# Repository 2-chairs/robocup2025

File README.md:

# robocup2025
# Team 2-Chairs - RoboCup Singapore Soccer Open Junior 

*Repository for the official electronic, mechanical, and software files of Team 2-Chairs.*

## About

This repository is for **Team 2-Chairs**, a Singapore RoboCup Open Soccer Junior team, and includes relevant design files and resources.

## Repository Structure

- **Electronics/** - PCB designs, schematics, and component footprints. (Note: regarding layer1 and layer3 pcb files, a critical mistake had been made where the Xiao Esp32c3 was powered through 3v3 pin with 3v3, when it should have been through 5v VIN pin with 5v; regarding layer3 the camera should be powered through 5v instead of 3v3 too)
- **Mechanical/** - 3D-printable files in **.3MF** and **.STL** formats; includes rendered images of the robot and its mirrored counterpart for reference. 
- **Code/** - Firmware and control software for the robot. (sub-par quality, some code untested)
- **Logo/** - Official team branding and design assets.

## Credits 
In the grand tapestry of our design endeavor, we owe a debt of profound gratitude to the esteemed teams of Sentinels Robotics, ducc. & Butter Chicken, whose brilliant schematics and designs (and potentially code) have guided our efforts.

## License & Copyright

© 2025 Team 2-Chairs. All rights reserved, except where otherwise stated. 

<p xmlns:cc="http://creativecommons.org/ns#" ><a rel="cc:attributionURL" href="https://github.com/2-chairs/robocup2025">This work</a> by <span property="cc:attributionName">Ng Chen-Xuan, Euston Tan, Chen YiKai</span> is licensed under <a href="https://creativecommons.org/licenses/by-nc-sa/4.0/?ref=chooser-v1" target="_blank" rel="license noopener noreferrer" style="display:inline-block;">Creative Commons Attribution-NonCommercial-ShareAlike 4.0 International</a></p>

---

**"Two chairs, twice the betterness"**

*Written by ChatGPT, Edited by human*

<p>Retired as of 6 April 2025</p>

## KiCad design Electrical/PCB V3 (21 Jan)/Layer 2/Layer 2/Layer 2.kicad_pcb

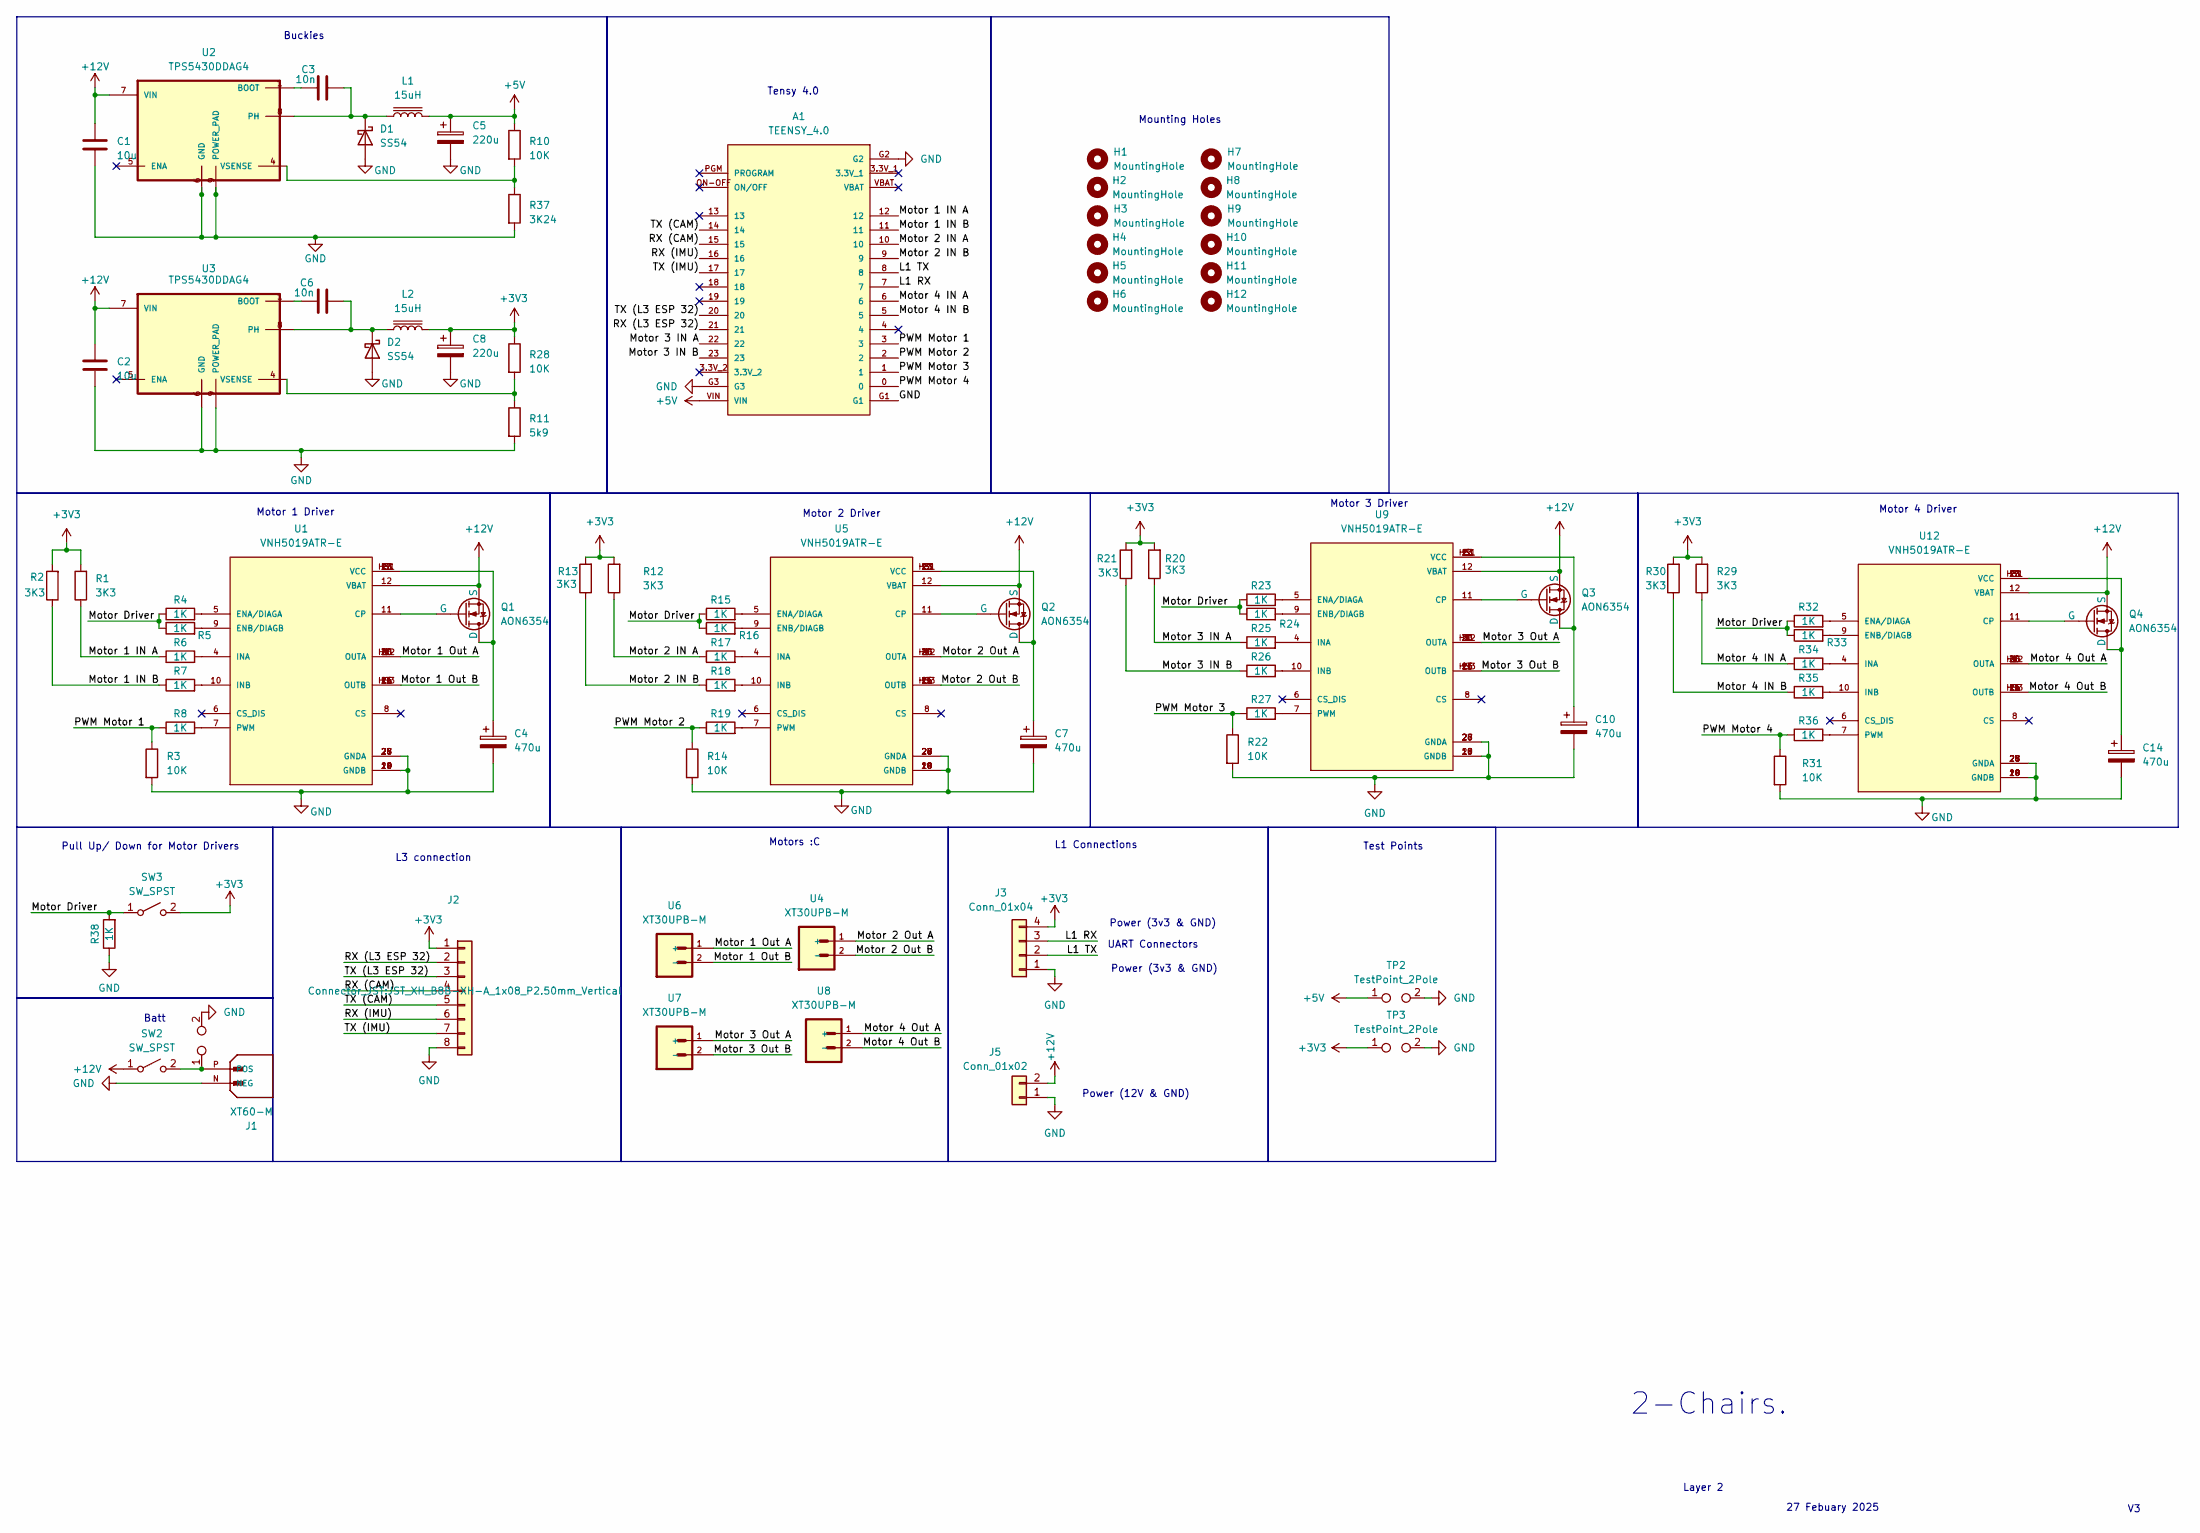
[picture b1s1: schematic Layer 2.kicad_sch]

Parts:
A1: TEENSY_4.0; MODULE_DEV-15583
C1, C2: 10u; C_0603_1608Metric
C3, C6: 10n; C_0603_1608Metric
C4, C7, C10, C14: 470u; CP_Radial_D8.0mm_P3.50mm; LCSC C5162352
C5, C8: 220u; CP_EIA-7343-15_Kemet-W_Pad2.25x2.55mm_HandSolder
D1, D2: SS54; DIOM5025X220N
H1, H2, H3, H4, H5, H6, H7, H8, H9, H10, H11, H12: MountingHole; MountingHole_3.2mm_M3_DIN965_Pad
J1: XT60-M; AMASS_XT60-M; PARTREV V1.2
J2: Conn_02x04_Odd_Even; JST_XH_B8B-XH-A_1x08_P2.50mm_Vertical
J3: Conn_01x04; JST_XH_B4B-XH-A_1x04_P2.50mm_Vertical
J5: Conn_01x02; SolderWire-0.1sqmm_1x02_P3.6mm_D0.4mm_OD1mm
L1, L2: 15uH; 0630 One Piece Inductor
Q1, Q2, Q3, Q4: AON6354; 8-DFN (5x6)
R1, R2, R12, R13, R20, R21, R29, R30: 3K3; res0603
R3, R14, R22, R31: 10K; res0603
R4, R5, R6, R7, R8, R15, R16, R17, R18, R19, R23, R24, R25, R26, R27, R32, R33, R34, R35, R36, R38: 1K; res0603
R10, R28: 10K; R_0603_1608Metric
R11: 5k9; R_0603_1608Metric
R37: 3K24; R_0603_1608Metric
SW2: SW_SPST; AMASS_XT30PW-M_1x02_P2.50mm_Horizontal
SW3: SW_SPST; JST_XH_B2B-XH-A_1x02_P2.50mm_Vertical
TP1: TestPoint_2Pole; 14 AWG Testpoint (Compact)
TP2, TP3: TestPoint_2Pole; 14 AWG Testpoint (Vertical)
U1, U5, U9, U12: VNH5019ATR-E; fixed -onenew-newer-newest; PARTREV 11
U2, U3: TPS5430DDAG4; TI_SO-PowerPAD-8
U4, U6, U7, U8: XT30UPB-M

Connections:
+3V3: C8.1, J2.1, J3.4, L2.2, R1.2, R2.2, R12.2, R13.2, R20.2, R21.2, R28.1, R29.2, R30.2, SW3.2 (B), TP3.1
+5V: A1.VIN, C5.1, L1.2, R10.1, TP2.1
+12V: C1.1, C2.1, J5.2, Q1.1 (S), Q1.2 (S), Q1.3 (S), Q2.1 (S), Q2.2 (S), Q2.3 (S), Q3.1 (S), Q3.2 (S), Q3.3 (S), Q4.1 (S), Q4.2 (S), Q4.3 (S), SW2.1 (A), U1.12 (VBAT), U2.7 (VIN), U3.7 (VIN), U5.12 (VBAT), U9.12 (VBAT), U12.12 (VBAT)
/L1 RX: A1.7, J3.3
/L1 TX: A1.8, J3.2
/Motor 1 IN A: A1.12, R1.1, R6.1
/Motor 1 IN B: A1.11, R2.1, R7.1
/Motor 1 Out A: U1.1 (OUTA), U1.25 (OUTA), U1.30 (OUTA), U1.HS2 (OUTA), U6.1 (+)
/Motor 1 Out B: U1.15 (OUTB), U1.16 (OUTB), U1.21 (OUTB), U1.HS3 (OUTB), U6.2 (-)
/Motor 2 IN A: A1.10, R12.1, R17.1
/Motor 2 IN B: A1.9, R13.1, R18.1
/Motor 2 Out A: U4.1 (+), U5.1 (OUTA), U5.25 (OUTA), U5.30 (OUTA), U5.HS2 (OUTA)
/Motor 2 Out B: U4.2 (-), U5.15 (OUTB), U5.16 (OUTB), U5.21 (OUTB), U5.HS3 (OUTB)
/Motor 3 IN A: A1.22, R20.1, R25.1
/Motor 3 IN B: A1.23, R21.1, R26.1
/Motor 3 Out A: U7.1 (+), U9.1 (OUTA), U9.25 (OUTA), U9.30 (OUTA), U9.HS2 (OUTA)
/Motor 3 Out B: U7.2 (-), U9.15 (OUTB), U9.16 (OUTB), U9.21 (OUTB), U9.HS3 (OUTB)
/Motor 4 IN A: A1.6, R29.1, R34.1
/Motor 4 IN B: A1.5, R30.1, R35.1
/Motor 4 Out A: U8.1 (+), U12.1 (OUTA), U12.25 (OUTA), U12.30 (OUTA), U12.HS2 (OUTA)
/Motor 4 Out B: U8.2 (-), U12.15 (OUTB), U12.16 (OUTB), U12.21 (OUTB), U12.HS3 (OUTB)
/Motor Driver: R4.1, R5.1, R15.1, R16.1, R23.1, R24.1, R32.1, R33.1, R38.2, SW3.1 (A)
/PWM Motor 1: A1.3, R3.1, R8.1
/PWM Motor 2: A1.2, R14.1, R19.1
/PWM Motor 3: A1.1, R22.1, R27.1
/PWM Motor 4: A1.0, R31.1, R36.1
/RX (CAM): A1.15, J2.4
/RX (IMU): A1.16, J2.6
/RX (L3 ESP 32): A1.21, J2.2
/TX (CAM): A1.14, J2.5
/TX (IMU): A1.17, J2.7
/TX (L3 ESP 32): A1.20, J2.3
GND: A1.G1, A1.G2, A1.G3, C1.2, C2.2, C4.2, C5.2, C7.2, C8.2, C10.2, C14.2, D1.2 (A), D2.2 (A), J1.N (NEG), J2.8, J3.1, J5.1, R3.2, R11.2, R14.2, R22.2, R31.2, R37.2, R38.1, TP1.2, TP2.2, TP3.2, U1.18 (GNDB), U1.19 (GNDB), U1.20 (GNDB), U1.26 (GNDA), U1.27 (GNDA), U1.28 (GNDA), U2.6 (GND), U2.9 (POWER_PAD), U3.6 (GND), U3.9 (POWER_PAD), U5.18 (GNDB), U5.19 (GNDB), U5.20 (GNDB), U5.26 (GNDA), U5.27 (GNDA), U5.28 (GNDA), U9.18 (GNDB), U9.19 (GNDB), U9.20 (GNDB), U9.26 (GNDA), U9.27 (GNDA), U9.28 (GNDA), U12.18 (GNDB), U12.19 (GNDB), U12.20 (GNDB), U12.26 (GNDA), U12.27 (GNDA), U12.28 (GNDA)
unnamed: C4.1, Q1.5 (D), Q1.6 (D), Q1.7 (D), Q1.8 (D), Q1.9 (D), U1.3 (VCC), U1.13 (VCC), U1.23 (VCC), U1.HS1 (VCC)
unnamed: C7.1, Q2.5 (D), Q2.6 (D), Q2.7 (D), Q2.8 (D), Q2.9 (D), U5.3 (VCC), U5.13 (VCC), U5.23 (VCC), U5.HS1 (VCC)
unnamed: C10.1, Q3.5 (D), Q3.6 (D), Q3.7 (D), Q3.8 (D), Q3.9 (D), U9.3 (VCC), U9.13 (VCC), U9.23 (VCC), U9.HS1 (VCC)
unnamed: C14.1, Q4.5 (D), Q4.6 (D), Q4.7 (D), Q4.8 (D), Q4.9 (D), U12.3 (VCC), U12.13 (VCC), U12.23 (VCC), U12.HS1 (VCC)
unnamed: C3.2, D1.1 (K), L1.1, U2.8 (PH)
unnamed: C6.2, D2.1 (K), L2.1, U3.8 (PH)
unnamed: J1.P (POS), SW2.2 (B), TP1.1
unnamed: Q1.4 (G), U1.11 (CP)
unnamed: Q2.4 (G), U5.11 (CP)
unnamed: Q3.4 (G), U9.11 (CP)
unnamed: Q4.4 (G), U12.11 (CP)
unnamed: R4.2, U1.5 (ENA/DIAGA)
unnamed: R5.2, U1.9 (ENB/DIAGB)
unnamed: R6.2, U1.4 (INA)
unnamed: R7.2, U1.10 (INB)
unnamed: R8.2, U1.7 (PWM)
unnamed: C3.1, U2.1 (BOOT)
unnamed: R10.2, R37.1, U2.4 (VSENSE)
unnamed: C6.1, U3.1 (BOOT)
unnamed: R11.1, R28.2, U3.4 (VSENSE)
unnamed: R15.2, U5.5 (ENA/DIAGA)
unnamed: R16.2, U5.9 (ENB/DIAGB)
unnamed: R17.2, U5.4 (INA)
unnamed: R18.2, U5.10 (INB)
unnamed: R19.2, U5.7 (PWM)
unnamed: R23.2, U9.5 (ENA/DIAGA)
unnamed: R24.2, U9.9 (ENB/DIAGB)
unnamed: R25.2, U9.4 (INA)
unnamed: R26.2, U9.10 (INB)
unnamed: R27.2, U9.7 (PWM)
unnamed: R32.2, U12.5 (ENA/DIAGA)
unnamed: R33.2, U12.9 (ENB/DIAGB)
unnamed: R34.2, U12.4 (INA)
unnamed: R35.2, U12.10 (INB)
unnamed: R36.2, U12.7 (PWM)

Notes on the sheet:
Tensy 4.0
Motor 4 Driver
Power (12V & GND)
Motor 1 Driver
Power (3v3 & GND)
Motor 3 Driver
L3 connection
UART Connectors
Motors :C
27 Febuary 2025
Test Points
Buckies
Motor 2 Driver
Mounting Holes
Layer 2
2-Chairs.
Pull Up/ Down for Motor Drivers
Batt
L1 Connections

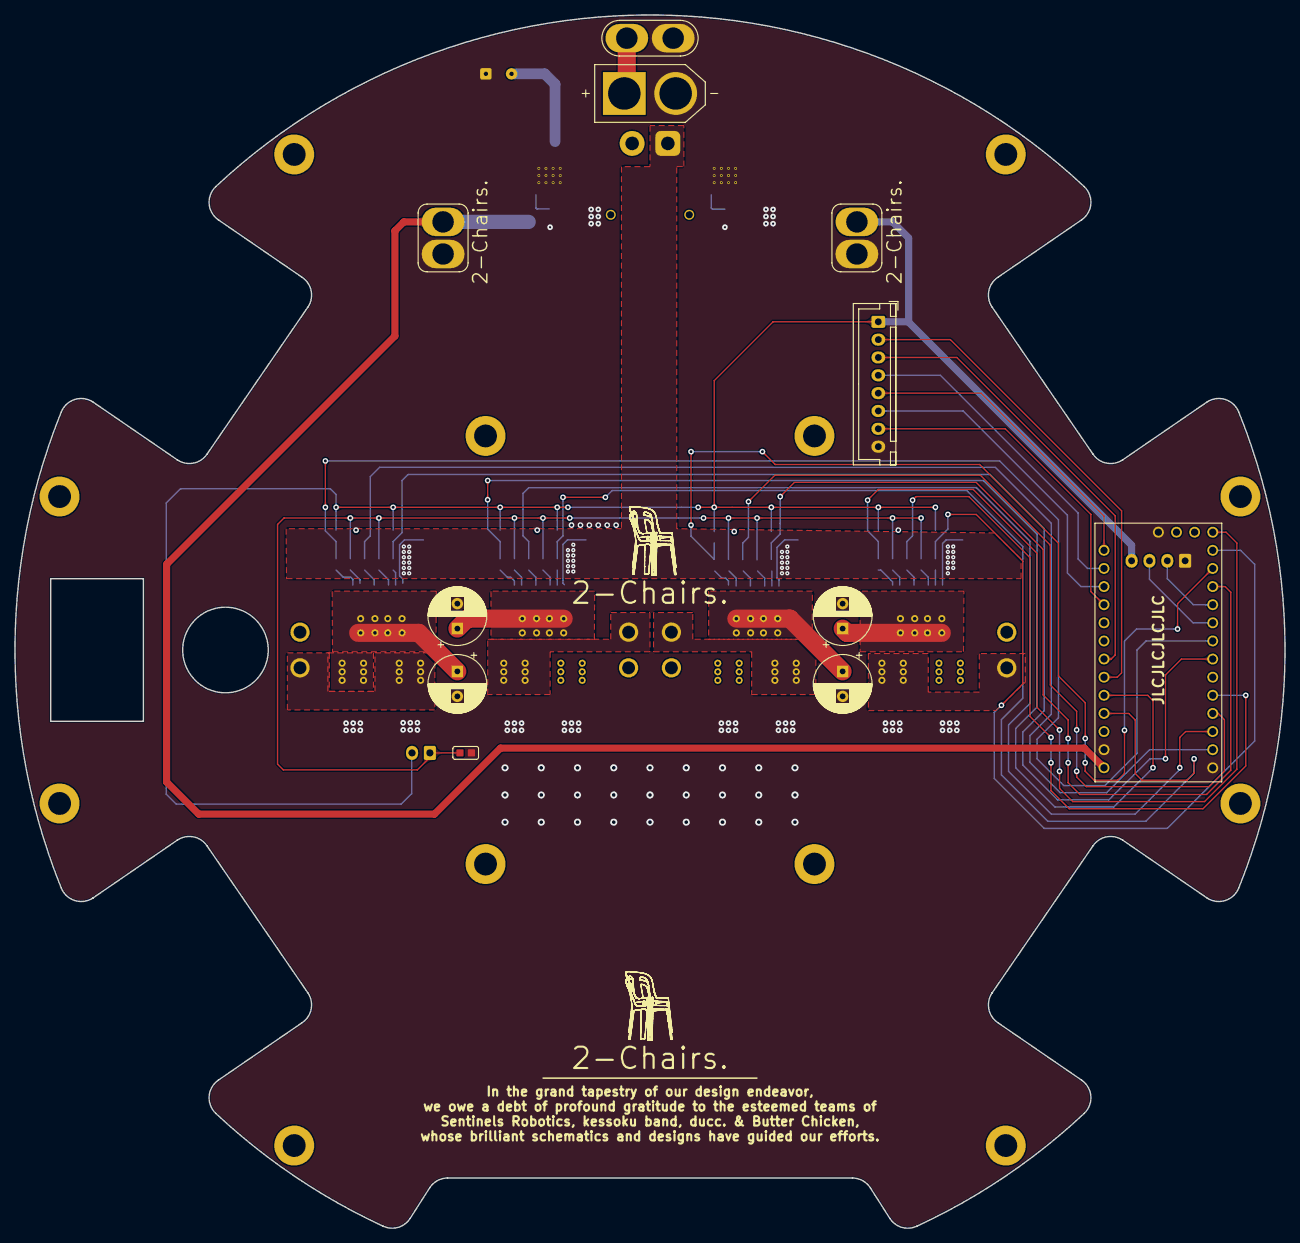
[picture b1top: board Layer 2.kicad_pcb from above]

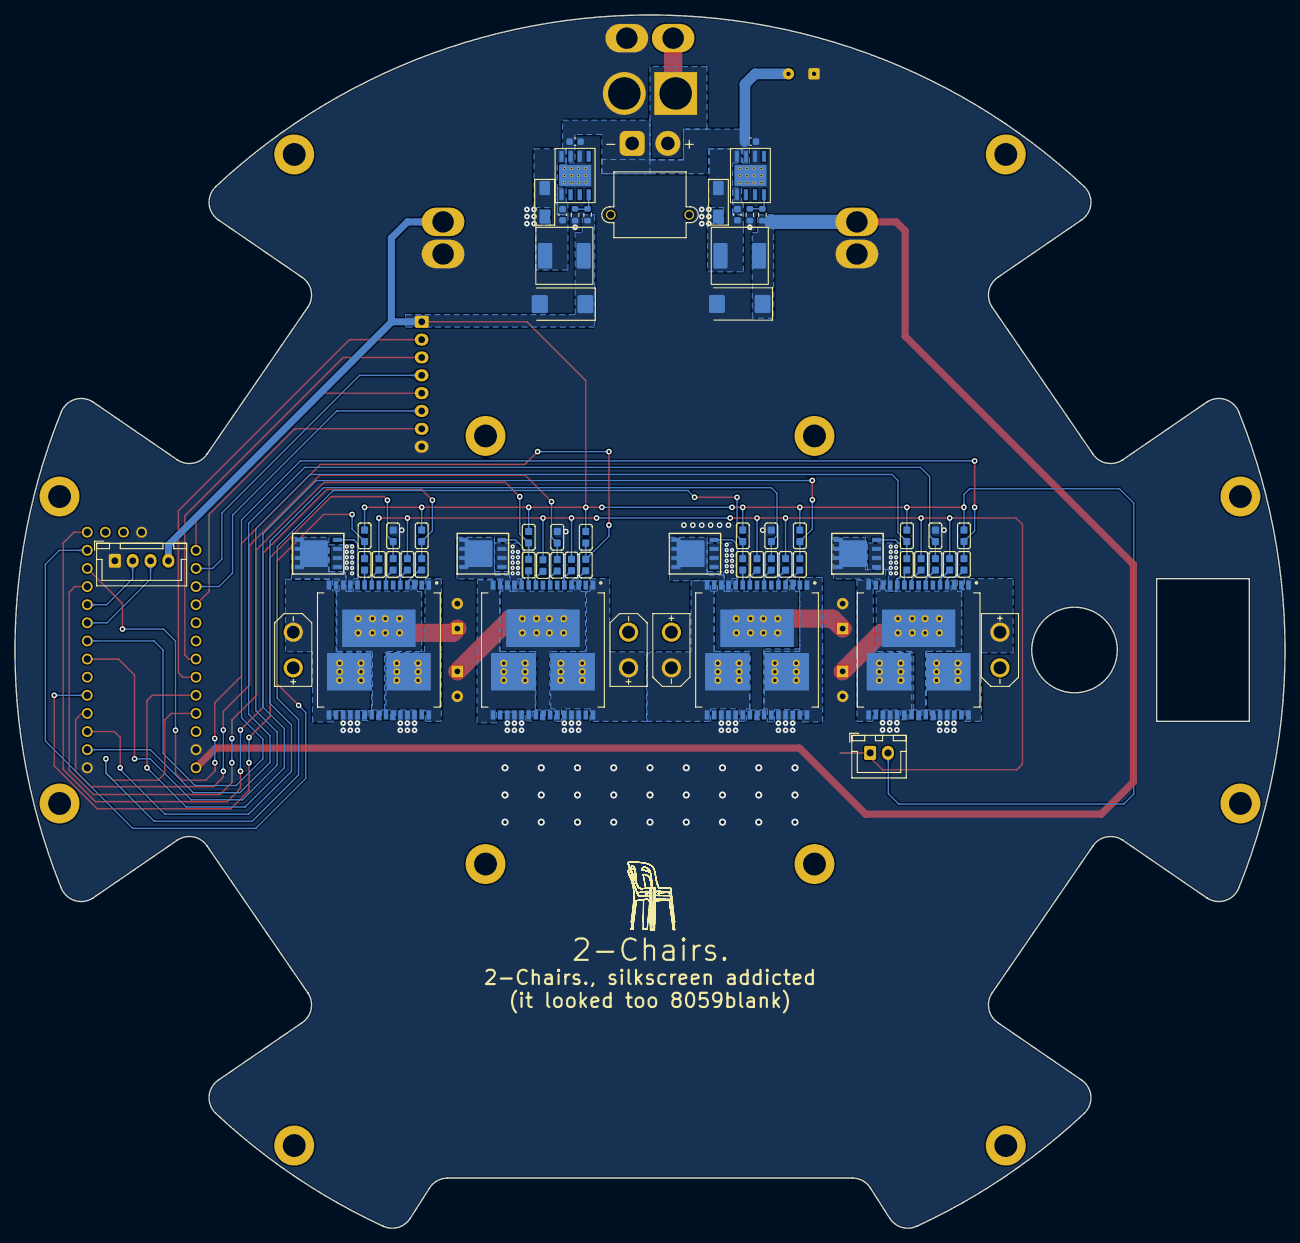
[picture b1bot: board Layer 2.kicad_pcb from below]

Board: 2 copper layers, 178.0 x 170.0 mm, 87 parts (64 on the bottom side), 68 nets.

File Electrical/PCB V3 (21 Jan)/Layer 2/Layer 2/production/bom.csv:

Designator,Footprint,Quantity,Value,LCSC Part #
A1,MODULE_DEV-15583,1,TEENSY_4.0,
"C1, C2",0603,2,10u,
"C10, C14, C4, C7",CP_Radial_D8.0mm_P3.50mm,4,470u,C5162352
"C3, C6",0603,2,10n,
"C5, C8",CP_EIA-7343-15_Kemet-W_Pad2.25x2.55mm_HandSolder,2,220u,
"D1, D2",DIOM5025X220N,2,SS54,
J1,AMASS_XT60-M,1,XT60-M,
J2,JST_XH_B8B-XH-A_1x08_P2.50mm_Vertical,1,Conn_02x04_Odd_Even,
J3,JST_XH_B4B-XH-A_1x04_P2.50mm_Vertical,1,Conn_01x04,
J5,SolderWire-0.1sqmm_1x02_P3.6mm_D0.4mm_OD1mm,1,Conn_01x02,
"L1, L2",0630 One Piece Inductor,2,15uH,
"Q1, Q2, Q3, Q4",8-DFN (5x6),4,AON6354,
"R1, R12, R13, R2, R20, R21, R29, R30",res0603,8,3K3,
"R10, R28",0603,2,10K,
R11,0603,1,5k9,
"R14, R22, R3, R31",res0603,4,10K,
"R15, R16, R17, R18, R19, R23, R24, R25, R26, R27, R32, R33, R34, R35, R36, R38, R4, R5, R6, R7, R8",res0603,21,1K,
R37,0603,1,3K24,
SW2,AMASS_XT30PW-M_1x02_P2.50mm_Horizontal,1,SW_SPST,
SW3,JST_XH_B2B-XH-A_1x02_P2.50mm_Vertical,1,SW_SPST,
TP1,14 AWG Testpoint (Compact),1,TestPoint_2Pole,
"TP2, TP3",14 AWG Testpoint (Vertical),2,TestPoint_2Pole,
"U1, U12, U5, U9",fixed -onenew-newer-newest,4,VNH5019ATR-E,
"U2, U3",TI_SO-PowerPAD-8,2,TPS5430DDAG4,
"U4, U6, U7, U8",XT30UPB-M,4,XT30UPB-M,

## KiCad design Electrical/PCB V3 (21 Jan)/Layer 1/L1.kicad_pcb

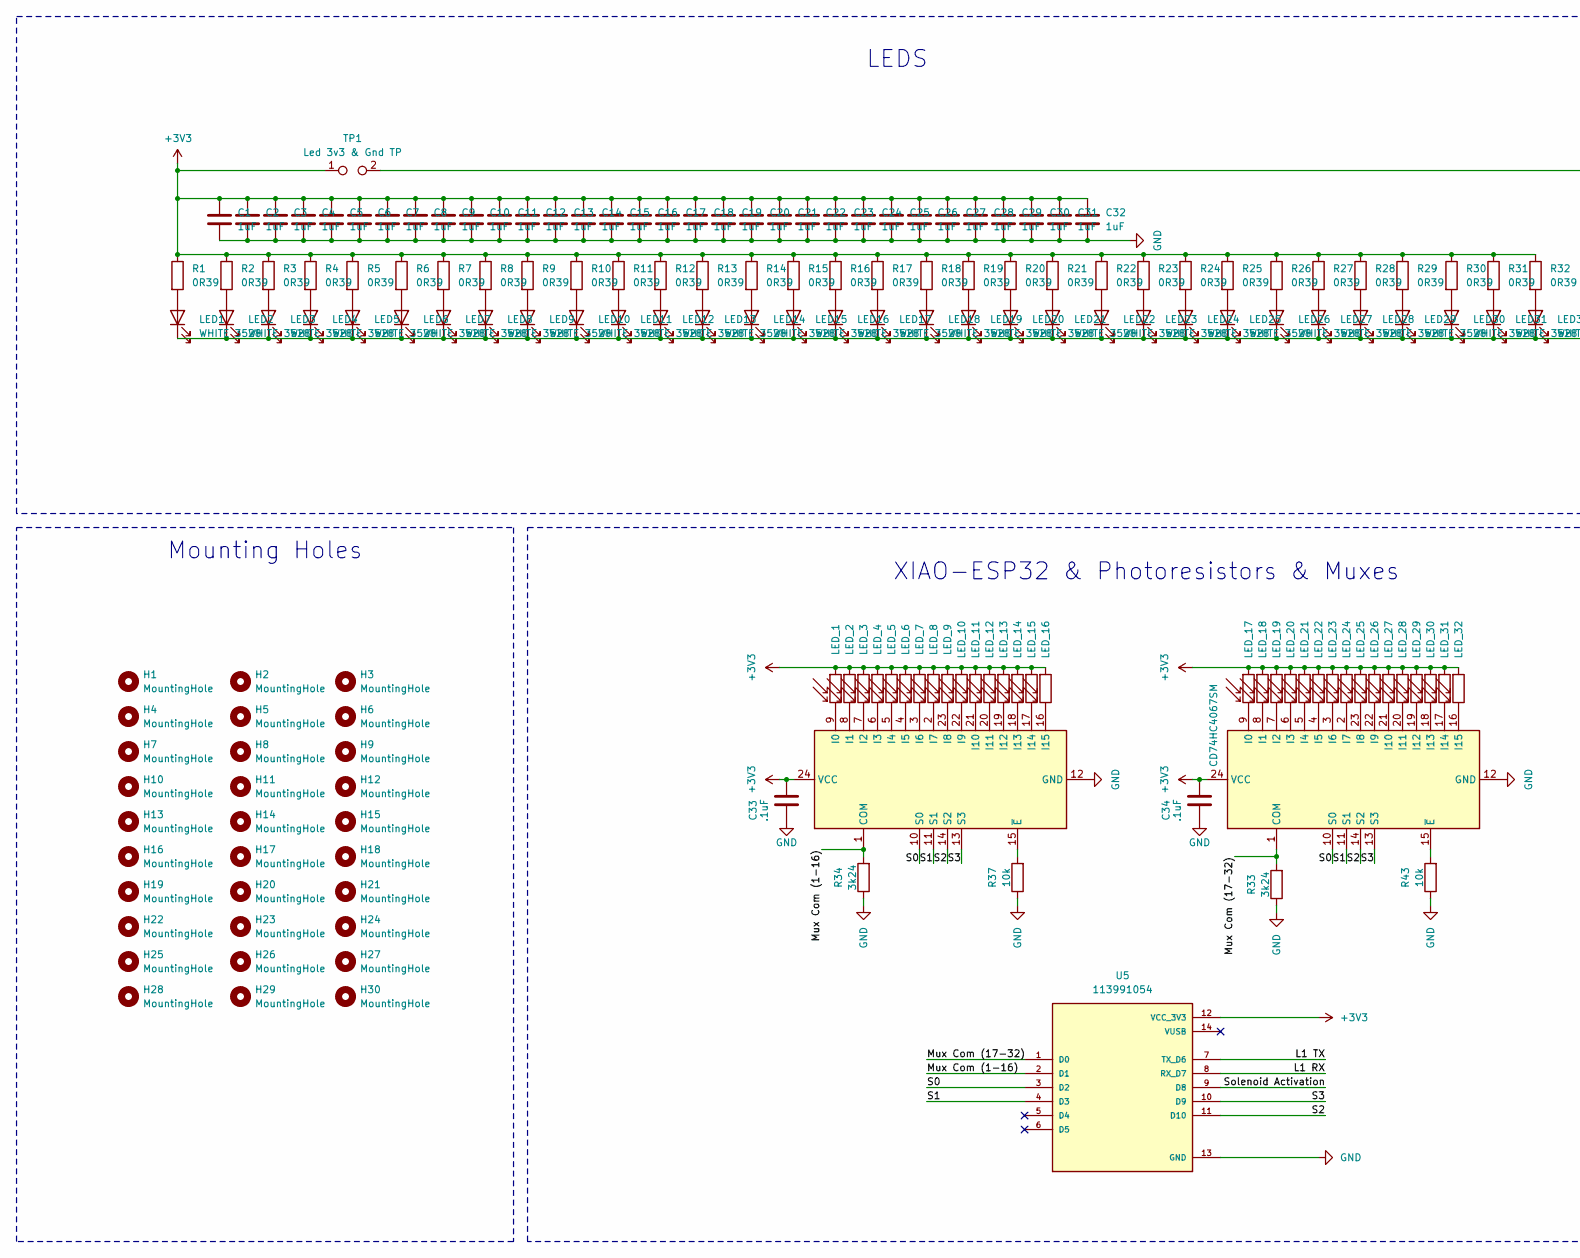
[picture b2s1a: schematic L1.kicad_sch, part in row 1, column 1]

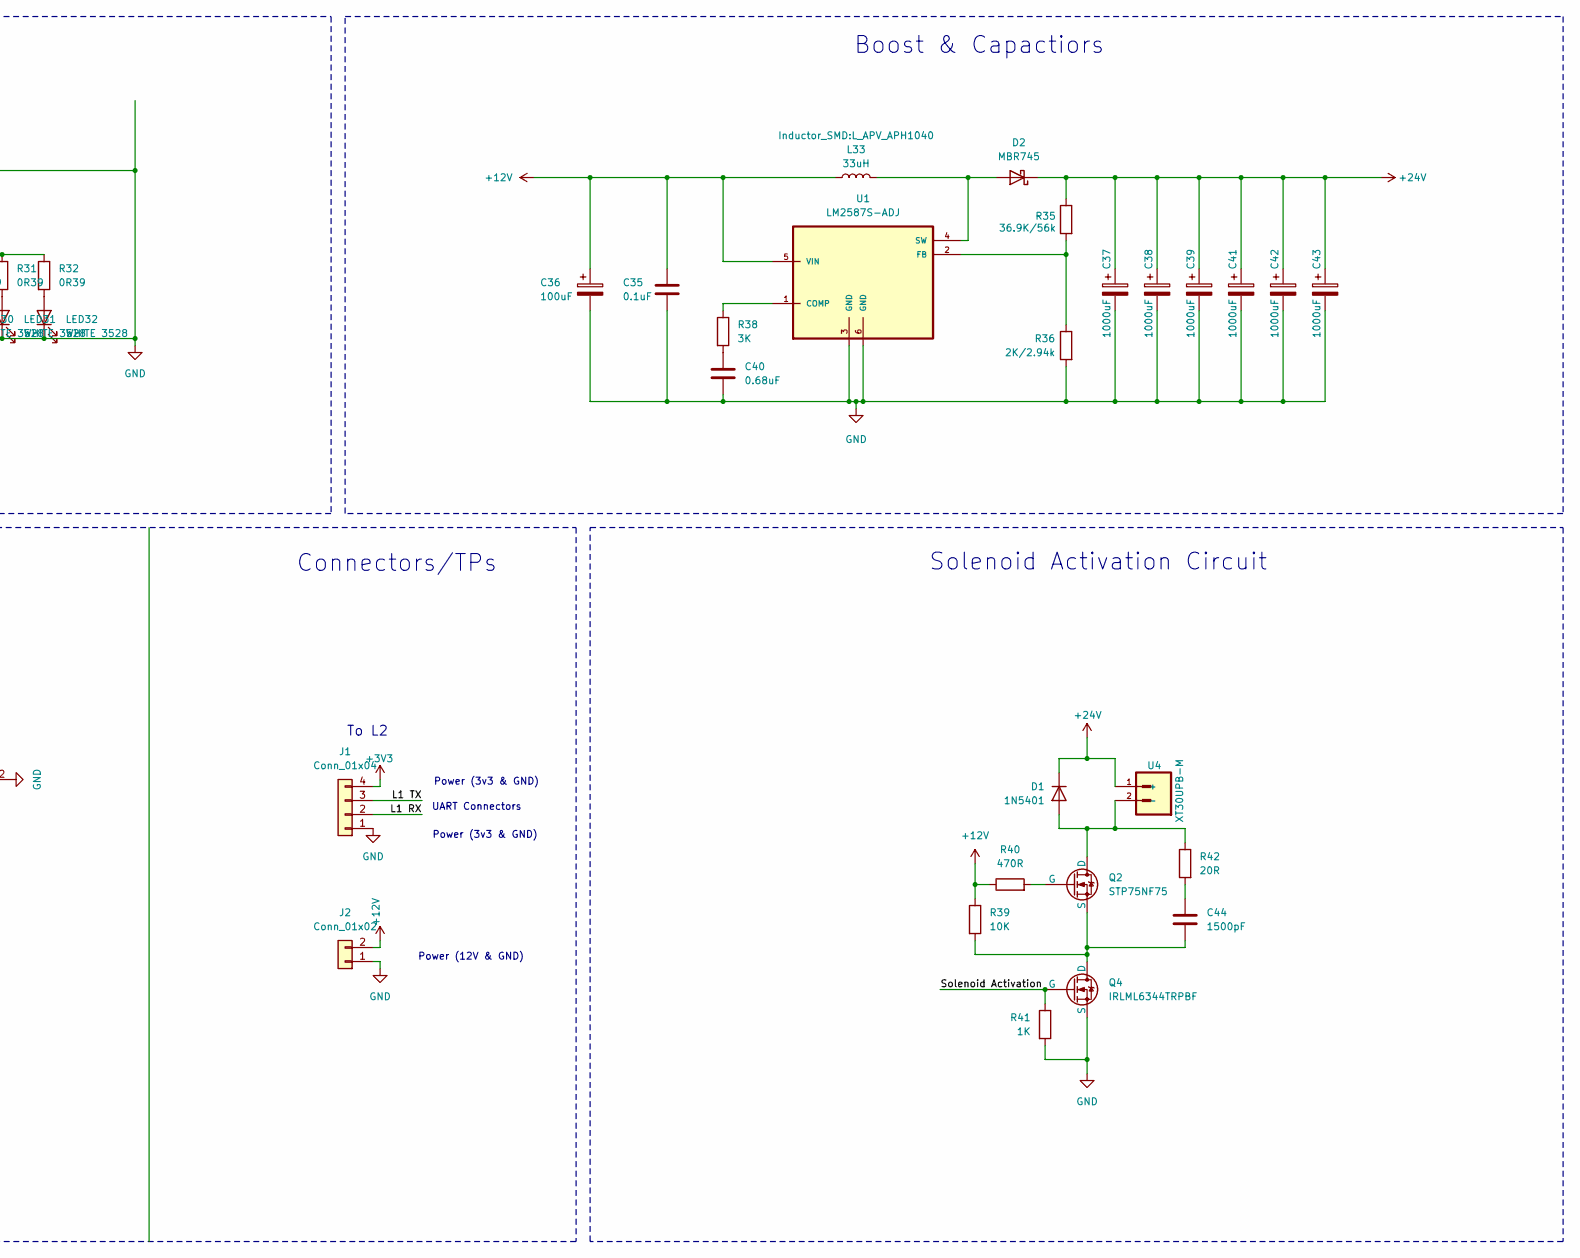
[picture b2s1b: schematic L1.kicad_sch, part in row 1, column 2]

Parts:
C1, C2, C3, C4, C5, C6, C7, C8, C9, C10, C11, C12, C13, C14, C15, C16, C17, C18, C19, C20, C21, C22, C23, C24, C25, C26, C27, C28, C29, C30, C31, C32: 1uF; C_0603_1608Metric
C33, C34: .1uF; C_0603_1608Metric
C35: 0.1uF; C_0603_1608Metric; LCSC C3011705
C36: 100uF; CP_Radial_D8.0mm_P3.50mm; LCSC C249586
C37, C38, C39, C41, C42, C43: 1000uF; CP_Radial_D16.0mm_P7.50mm; LCSC C249586
C40: 0.68uF; C_0603_1608Metric; LCSC C59782
C44: 1500pF; C_0603_1608Metric; LCSC C107060
D1: 1N5401; D_DO-201AD_P15.24mm_Horizontal; LCSC C179506
D2: MBR745; TO-220-2_Vertical
H1, H2, H3, H4, H5, H6, H7, H8, H9, H10, H11, H12, H13, H14, H15, H16, H17, H18, H19, H20, H21, H22, H23, H24, H25, H26, H27, H28, H29, H30: MountingHole; MountingHole_3.2mm_M3_DIN965_Pad
J1: Conn_01x04; JST_EH_B4B-EH-A_1x04_P2.50mm_Vertical
J2: Conn_01x02; AMASS_XT30UPB-M_1x02_P5.0mm_Vertical
L33: 33uH; L_APV_APH1040; LCSC C2875750
LED1, LED2, LED3, LED4, LED5, LED6, LED7, LED8, LED9, LED10, LED11, LED12, LED13, LED14, LED15, LED16, LED17, LED18, LED19, LED20, LED21, LED22, LED23, LED24, LED25, LED26, LED27, LED28, LED29, LED30, LED31, LED32: WHITE 3528; LED_PLCC_2835
LED_1, LED_2, LED_3, LED_4, LED_5, LED_6, LED_7, LED_8, LED_9, LED_10, LED_11, LED_12, LED_13, LED_14, LED_15, LED_16, LED_17, LED_18, LED_19, LED_20, LED_21, LED_22, LED_23, LED_24, LED_25, LED_26, LED_27, LED_28, LED_29, LED_30, LED_31, LED_32: R_Photo; XDCR_ALS-PT19-315C_L177_TR8
Q2: STP75NF75; TO-220-3_Vertical; Mouser Part Number 726-IPD050N10N5ATMA1; LCSC C13678
Q4: IRLML6344TRPBF; SOT95P237X112-3N; Mouser Part Number 942-IRLML6344TRPBF
R1, R2, R3, R4, R5, R6, R7, R8, R9, R10, R11, R12, R13, R14, R15, R16, R17, R18, R19, R20, R21, R22, R23, R24, R25, R26, R27, R28, R29, R30, R31, R32: 0R39; R_0603_1608Metric
R33, R34: 3k24; R_0603_1608Metric
R35: 36.9K/56k; C_0603_1608Metric; LCSC C23082
R36: 2K/2.94k; C_0603_1608Metric; LCSC C22843
R37, R43: 10k; R_0603_1608Metric
R38: 3K; C_0603_1608Metric; LCSC C137748
R39: 10K; R_0603_1608Metric; LCSC C25804
R40: 470R; R_0603_1608Metric; LCSC C21190
R41: 1K; R_0603_1608Metric; LCSC C21190
R42: 20R; R_0603_1608Metric; LCSC C22950
TP1: Led 3v3 & Gnd TP; testpoint_2pad_2-chairs.
U1: LM2587S-ADJ; VREG_TPS79625KTTR
U2, U3: CD74HC4067SM; SOP65P780X200-24N
U4: XT30UPB-M; AMASS_XT30U-M_1x02_P5.0mm_Vertical
U5: 113991054; XiaoSeeedStudioEsp32; PARTREV 23/05/2022

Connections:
+3V3: C1.1, C2.1, C3.1, C4.1, C5.1, C6.1, C7.1, C8.1, C9.1, C10.1, C11.1, C12.1, C13.1, C14.1, C15.1, C16.1, C17.1, C18.1, C19.1, C20.1, C21.1, C22.1, C23.1, C24.1, C25.1, C26.1, C27.1, C28.1, C29.1, C30.1, C31.1, C32.1, C33.2, C34.2, J1.4, LED_1.1, LED_2.1, LED_3.1, LED_4.1, LED_5.1, LED_6.1, LED_7.1, LED_8.1, LED_9.1, LED_10.1, LED_11.1, LED_12.1, LED_13.1, LED_14.1, LED_15.1, LED_16.1, LED_17.1, LED_18.1, LED_19.1, LED_20.1, LED_21.1, LED_22.1, LED_23.1, LED_24.1, LED_25.1, LED_26.1, LED_27.1, LED_28.1, LED_29.1, LED_30.1, LED_31.1, LED_32.1, R1.1, R2.1, R3.1, R4.1, R5.1, R6.1, R7.1, R8.1, R9.1, R10.1, R11.1, R12.1, R13.1, R14.1, R15.1, R16.1, R17.1, R18.1, R19.1, R20.1, R21.1, R22.1, R23.1, R24.1, R25.1, R26.1, R27.1, R28.1, R29.1, R30.1, R31.1, R32.1, TP1.1, U2.24 (VCC), U3.24 (VCC), U5.12 (VCC_3V3)
+12V: C35.1, C36.1, J2.2, L33.1, R39.1, R40.1, U1.5 (VIN)
+24V: C37.1, C38.1, C39.1, C41.1, C42.1, C43.1, D1.1 (K), D2.1 (K), R35.1, U4.1 (+)
/L1 RX: J1.2, U5.8 (RX_D7)
/L1 TX: J1.3, U5.7 (TX_D6)
/Mux Com (1-16): R34.2, U3.1 (COM), U5.2 (D1)
/Mux Com (17-32): R33.2, U2.1 (COM), U5.1 (D0)
/S0: U2.10 (S0), U3.10 (S0), U5.3 (D2)
/S1: U2.11 (S1), U3.11 (S1), U5.4 (D3)
/S2: U2.14 (S2), U3.14 (S2), U5.11 (D10)
/S3: U2.13 (S3), U3.13 (S3), U5.10 (D9)
/Solenoid Activation: Q4.1 (G), R41.1, U5.9 (D8)
GND: C1.2, C2.2, C3.2, C4.2, C5.2, C6.2, C7.2, C8.2, C9.2, C10.2, C11.2, C12.2, C13.2, C14.2, C15.2, C16.2, C17.2, C18.2, C19.2, C20.2, C21.2, C22.2, C23.2, C24.2, C25.2, C26.2, C27.2, C28.2, C29.2, C30.2, C31.2, C32.2, C33.1, C34.1, C35.2, C36.2, C37.2, C38.2, C39.2, C40.2, C41.2, C42.2, C43.2, J1.1, J2.1, LED1.1 (K), LED2.1 (K), LED3.1 (K), LED4.1 (K), LED5.1 (K), LED6.1 (K), LED7.1 (K), LED8.1 (K), LED9.1 (K), LED10.1 (K), LED11.1 (K), LED12.1 (K), LED13.1 (K), LED14.1 (K), LED15.1 (K), LED16.1 (K), LED17.1 (K), LED18.1 (K), LED19.1 (K), LED20.1 (K), LED21.1 (K), LED22.1 (K), LED23.1 (K), LED24.1 (K), LED25.1 (K), LED26.1 (K), LED27.1 (K), LED28.1 (K), LED29.1 (K), LED30.1 (K), LED31.1 (K), LED32.1 (K), Q4.2 (S), R33.1, R34.1, R36.2, R37.1, R41.2, R43.1, TP1.2, U1.3 (GND), U1.6 (GND), U2.12 (GND), U3.12 (GND), U5.13 (GND)
unnamed: C40.1, R38.2
unnamed: C44.1, R42.2
unnamed: D1.2 (A), Q2.2 (D), R42.1, U4.2 (-)
unnamed: D2.2 (A), L33.2, U1.4 (SW)
unnamed: LED1.2 (A), R1.2
unnamed: LED2.2 (A), R2.2
unnamed: LED3.2 (A), R3.2
unnamed: LED4.2 (A), R4.2
unnamed: LED5.2 (A), R5.2
unnamed: LED6.2 (A), R6.2
unnamed: LED7.2 (A), R7.2
unnamed: LED8.2 (A), R8.2
unnamed: LED9.2 (A), R9.2
unnamed: LED10.2 (A), R10.2
unnamed: LED11.2 (A), R11.2
unnamed: LED12.2 (A), R12.2
unnamed: LED13.2 (A), R13.2
unnamed: LED14.2 (A), R14.2
unnamed: LED15.2 (A), R15.2
unnamed: LED16.2 (A), R16.2
unnamed: LED17.2 (A), R17.2
unnamed: LED18.2 (A), R18.2
unnamed: LED19.2 (A), R19.2
unnamed: LED20.2 (A), R20.2
unnamed: LED21.2 (A), R21.2
unnamed: LED22.2 (A), R22.2
unnamed: LED23.2 (A), R23.2
unnamed: LED24.2 (A), R24.2
unnamed: LED25.2 (A), R25.2
unnamed: LED26.2 (A), R26.2
unnamed: LED27.2 (A), R27.2
unnamed: LED28.2 (A), R28.2
unnamed: LED29.2 (A), R29.2
unnamed: LED30.2 (A), R30.2
unnamed: LED31.2 (A), R31.2
unnamed: LED32.2 (A), R32.2
unnamed: Q2.1 (G), R40.2
unnamed: C44.2, Q2.3 (S), Q4.3 (D), R39.2
unnamed: R38.1, U1.1 (COMP)
unnamed: R35.2, R36.1, U1.2 (FB)
unnamed: LED_17.2, U2.9 (I0)
unnamed: LED_18.2, U2.8 (I1)
unnamed: LED_19.2, U2.7 (I2)
unnamed: LED_20.2, U2.6 (I3)
unnamed: LED_21.2, U2.5 (I4)
unnamed: LED_22.2, U2.4 (I5)
unnamed: LED_23.2, U2.3 (I6)
unnamed: LED_24.2, U2.2 (I7)
unnamed: LED_25.2, U2.23 (I8)
unnamed: LED_26.2, U2.22 (I9)
unnamed: LED_27.2, U2.21 (I10)
unnamed: LED_28.2, U2.20 (I11)
unnamed: LED_29.2, U2.19 (I12)
unnamed: LED_30.2, U2.18 (I13)
unnamed: LED_31.2, U2.17 (I14)
unnamed: LED_32.2, U2.16 (I15)
unnamed: R43.2, U2.15 (~E)
unnamed: LED_1.2, U3.9 (I0)
unnamed: LED_2.2, U3.8 (I1)
unnamed: LED_3.2, U3.7 (I2)
unnamed: LED_4.2, U3.6 (I3)
unnamed: LED_5.2, U3.5 (I4)
unnamed: LED_6.2, U3.4 (I5)
unnamed: LED_7.2, U3.3 (I6)
unnamed: LED_8.2, U3.2 (I7)
unnamed: LED_9.2, U3.23 (I8)
unnamed: LED_10.2, U3.22 (I9)
unnamed: LED_11.2, U3.21 (I10)
unnamed: LED_12.2, U3.20 (I11)
unnamed: LED_13.2, U3.19 (I12)
unnamed: LED_14.2, U3.18 (I13)
unnamed: LED_15.2, U3.17 (I14)
unnamed: LED_16.2, U3.16 (I15)
unnamed: R37.2, U3.15 (~E)

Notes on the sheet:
Power (12V & GND)
LEDS
XIAO-ESP32 & Photoresistors & Muxes
Power (3v3 & GND)
To L2
UART Connectors
Boost & Capactiors
Solenoid Activation Circuit
Connectors/TPs
Mounting Holes
